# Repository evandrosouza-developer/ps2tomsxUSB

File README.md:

# STM32: PS/2 to MSX Keyboard Converter

# Introduction

First of all, to people who use or had used MSX, welcome, bem-vindos, welkom, bienvenidos, добро пожаловать, 환영하다 and ようこそ, to visit my repository.

Instead of an application to this old japanese home computer standards is not so widely useful in nowadays, I made this to learn STM32 hardware and software technics, and I'd like it to be useful and let us back in time and make our MSX computer jewlers work with joyful to our pleasure.

The MSX Keyboard enviroment components (PS/2 to MSX Keyboard Converter, MSX Keyboard subsystem Emulator and the modifyed TIO - A simple terminal) are fully functional and debugged and here I used a lot of concepts that, IMHO could be used as idea sources to your applications.  

# Lets do it!

This interface has the function of connect a PS/2 keyboard (or a USB one in compatibility mode) as source to TTL zero (low state) active matrix based computers, like MSX and ZX-Spectrum as destination. It is meant to connect a keyboard, which only provides a PS/2 connector, to a MSX (or any one that have a up to 15 active columns and reads zeroes througth 8 bits - up to 15 x 8 matrix) computer.  

The differencial of this design is to allow user to customize and do a hot update of the database layout of this PS/2 Keyboard, as like as the MSX one, through an USB (or async serial) interface and a tty terminal on host side.  

The default database mappings for the keyboard layouts are:

- Source (PS/2 keyboard): 275 (ABNT2 layout - Brazilian Technical Norms Association);

- Target: Brazilian Sharp/Epcom Hotbit HB8000 MSX.  

This firmware was made to support both Blue Pill and Black Pill and it is part of the PS/2 to MSX Converter Enviroment, all of them in my github page, that consists:
```
1)The PS/2 to MSX Keyboard Converter itself, which contains:
1.1) The firmware with source files;
1.2) Doxygen full firmware documentation;
1.3) Schematics and PCB design:
1.3.1) Electronics part Schematics with Kicad files;
1.3.2) Single sided PCB layout with Kicad files and complete set of Gerber files;
1.4) The performance tests of this one are inside the PS/2 to MSX Converter Tester folder.

2)The PS/2 to MSX Converter Tester, which contains:
2.1) The firmware with source files;
2.2) Doxygen full firmware documentation;
2.3) Schematics design with Kicad files;
2.4) The performance tests of the PS/2 to MSX Keyboard Converter are located here.

3) Open tool to create/modify the Database (Translation tables to map from PS/2 Scan Codes to MSX Matrix Codes)
in excel, but it has compatible macros to be executed by Libre Office, Open Office and so on.

4) Tini TTY I/O - `tio` (Linux app with source files) to communicate with console and easily allowing the
user to use it with different keyboard layouts and languages.
```
In case of STM32F103C8T6 (Flash 64K RAM 20K) Blue Pill, you have to aplly STM32F103C6T6 (Flash 32K RAM 10K) without change anything else.

In case of Black Pill, the base system is STM32F401CCU6 so, to use a more memory one, just follow the same instructions here.

This firmware powers and has been tested on the following Windows PS/2 keyboards, with brazilian 275 layout:  
- Compaq RT235BTWBR;  
- Clone KE11090749;  
- Clone #09100.  
  
The inspiring code for the PS/2 module, a PS/2 to USB keyboard adapter, was originally developed based on Cherry G80-3000LSMDE.  

# Why not STM32F103C8T6 Blue Pill?

Because Blue Pill has no 5V tolerant pins available to connect PS/2 + MSX + Serial + USB, unlike Black Pill. Even serial (UART) was feasibled using a 3.3V only port.  
Although, this limitation came with a bonus: The need of a cheaper and greater availability 32KB flash MCU: STM32F103C6T6  

# Dependencies

- `libopencm3`
- `arm-none-eabi-gcc`
- `arm-none-eabi-binutils`

If you plan to debug:
- `arm-none-eabi-gdb`
- `stlink + openocd`

Obs.: If you plan to keep only one copy of LibopenCM3 in your computer, I strongly suggest you to setup the variable OPENCM3_DIR in our system enviroment.

# Preparations

After cloning the repository you need to make the following procedure:

Go to libopencm3 you cloned (eg: cd libopencm3) and make it to be useful by typing:

```
cd libopencm3
make TARGETS='stm32/f1 stm32/f4'
```

Go to this ps2-msx-kb-conv (PS/2 to MSX Converter) project folder and assure that you choose the right target MCU in the system.h file line 69, and make, as follows:

With a plain text editor:
```
#define MCU                       STM32F401
or
#define MCU                       STM32F103
```

Save the file, and,  
Create the image file to be sent to the MCU (Micro Controller Unit):

```
make
```
The created image, compiled with the Arm GNU Toolchain 14.2.Rel1 Released: December 10, 2024, on an aarch64 debian bullseye linux computer is created with the following characteristics, according to the choosen MCU:
```
arm-none-eabi-size ps2-msx-kb-convF4.elf
   text	   data	    bss	    dec	    hex	filename
35796	    384	   8436	  44616	   ae48	ps2-msx-kb-convF4.elf

arm-none-eabi-size ps2-msx-kb-convF1.elf
   text	   data	    bss	    dec	    hex	filename
  27152	    352	   2492	  29996	   752c	ps2-msx-kb-convF1.elf

```

# Hardware and Setup

## Hardware and Setup for Blue Pill:

You will obviously need a STM32F103C6T6 or a STM32F103C8T6 (F1 chip). I have used chinese blue pills. The software was made aiming in use of compatible processors, like GD32 for example. 
  
The software was made considering 8.000Mhz oscillator crystal, to clock the STM32 microcontroller chip at 72MHz. I tested with both STM32F103C6T6 and STM32F103C8T6.

The connections are:

1) PS/2 Keyboard:

- Clock Pin PA12 - Connect to PS/2 mini-din 45322 pin 5 throught R16;  
- Data Pin PA9 - Connect to PS/2 mini-din pin 1 throught R18;    
- +5V PS/2 power - Connect collector of Q2 to mini-din pin 4;  
- GND - Connect GNDD (Digital Ground) to mini-din pin 3.

2) MSX computer:

Obs.: You have to access PPI Ports B0 to B7 (Lines X0 to X7), Port C0 to C3 (Y0 to Y3), Port C6 (Caps Lock, pin 11 of DIP package), and for Russian, Arabic, Korean and Japanese Computers (Cyrillic and Kana alphabets), you have to get access to YM2149/AY3-8910 IOB7, pin 6 of DIP package, or, if your MSX is equipped with S1985(MSX-SYSTEM II), you have to have granted access to pins 71 and 72.  
- Y3 - Connect to MSX PPI 8255 Signal PC3 (HB-8000 CI-15 Pin 17 / XP-800 CI-4 Pin 17);  
- Y2 - Connect to MSX PPI 8255 Signal PC2 (HB-8000 CI-15 Pin 16 / XP-800 CI-4 Pin 16);  
- Y1 - Connect to MSX PPI 8255 Signal PC1 (HB-8000 CI-15 Pin 15 / XP-800 CI-4 Pin 15);  
- Y0 - Connect to MSX PPI 8255 Signal PC0 (HB-8000 CI-15 Pin 14 / XP-800 CI-4 Pin 14);  
- X7 - Connect to MSX PPI 8255 Signal PB7 (HB-8000 CI-15 Pin 25 / XP-800 CI-4 Pin 25);  
- X6 - Connect to MSX PPI 8255 Signal PB6 (HB-8000 CI-15 Pin 24 / XP-800 CI-4 Pin 24);  
- X5 - Connect to MSX PPI 8255 Signal PB5 (HB-8000 CI-15 Pin 23 / XP-800 CI-4 Pin 23);  
- X4 - Connect to MSX PPI 8255 Signal PB4 (HB-8000 CI-15 Pin 22 / XP-800 CI-4 Pin 22);  
- X3 - Connect to MSX PPI 8255 Signal PB3 (HB-8000 CI-15 Pin 21 / XP-800 CI-4 Pin 21);  
- X2 - Connect to MSX PPI 8255 Signal PB2 (HB-8000 CI-15 Pin 20 / XP-800 CI-4 Pin 20);  
- X1 - Connect to MSX PPI 8255 Signal PB1 (HB-8000 CI-15 Pin 19 / XP-800 CI-4 Pin 19);  
- X0 - Connect to MSX PPI 8255 Signal PB0 (HB-8000 CI-15 Pin 18 / XP-800 CI-4 Pin 18);  
- Caps LED - Connect to MSX PPI 8255 Signal PC6 (HB-8000 CI-15 Pin 11 / XP-800 CI-4 Pin 11) or S1985 Pin 71;  
- Kana LED - Connect to MSX YM2149 or AY3-8910 IOB7, pin 6 of DIP package or S1985 Pin 72. If the MSX doesn't have this indicator LED, you can leave it open, as it already has an internal pull-up connection. In brazilian, argentinian and most european MSX, for example, this is a non-connect pin.   

3) Serial console:
 It is the only option for console available if you are using Blue Pill. See "Why not STM32F103C8T6 Blue Pill?".

  The connection is needed only to update internal PS/2 to MSX key mapping Database.  
  Config: 115200, 8, n, 1 (115200 bps, 8 bits, no parity, 1 stop bit);  
  Tx: A2  
  Rx: A3  

  *******************************************************************************************************

  Obs.: It is a only 3.3V port, compatible to TTL levels, so do NOT use it with "1" level higher than 3.3V!!

  *******************************************************************************************************

 About physical connection: The connection has to be done with TX of your host system connected with RX of the PS/2 to MSX Keyboard Converter (device), and the device's TX has to be connected to host's RX.

## Hardware and Setup for Black Pill:

You will obviously need a a F4 chip (STM32F401CCU6 or up, if using WeAct Mini F4 compatible black pill).

The software was made considering 25.000Mhz oscillator crystal, to clock the STM32 microcontroller chip at 84MHz. I tested with both STM32F401CCU6 and STM32F401CDU6.

The connections are:

1) PS/2 Keyboard (J3- PS/2 Port) :

- PS/2 power - Pin 1 - Connect to PS/2 mini-din 45322 pin 4;  
- Clock      - Pin 2 - Connect to PS/2 mini-din 45322 pin 5;  
- Data       - Pin 3 - Connect to PS/2 mini-din 45322 pin 1;  
- GNDD       - Pin 4 - Connect to PS/2 mini-din 45322 pin 3.  

2) MSX computer:

Obs.: You have to access PPI Ports B0 to B7 (Lines X0 to X7), Port C0 to C3 (Y0 to Y3), Port C6 (Caps Lock, pin 11 of DIP package), and for Russian and Japanese Computers (Cyrillic and Kana alphabets), you have to get access to YM2149/AY3-8910 IOB7, pin 6 of DIP package, or, if your MSX is equipped with S1985(MSX-SYSTEM II), you have to have granted access to pins 71 and 72.  

- Y3 - Connect to MSX PPI 8255 Signal PC3 (HB-8000 CI-15 Pin 17 / XP-800 CI-4 Pin 17);  
- Y2 - Connect to MSX PPI 8255 Signal PC2 (HB-8000 CI-15 Pin 16 / XP-800 CI-4 Pin 16);  
- Y1 - Connect to MSX PPI 8255 Signal PC1 (HB-8000 CI-15 Pin 15 / XP-800 CI-4 Pin 15);  
- Y0 - Connect to MSX PPI 8255 Signal PC0 (HB-8000 CI-15 Pin 14 / XP-800 CI-4 Pin 14);  
- X7 - Connect to MSX PPI 8255 Signal PB7 (HB-8000 CI-15 Pin 25 / XP-800 CI-4 Pin 25);  
- X6 - Connect to MSX PPI 8255 Signal PB6 (HB-8000 CI-15 Pin 24 / XP-800 CI-4 Pin 24);  
- X5 - Connect to MSX PPI 8255 Signal PB5 (HB-8000 CI-15 Pin 23 / XP-800 CI-4 Pin 23);  
- X4 - Connect to MSX PPI 8255 Signal PB4 (HB-8000 CI-15 Pin 22 / XP-800 CI-4 Pin 22);  
- X3 - Connect to MSX PPI 8255 Signal PB3 (HB-8000 CI-15 Pin 21 / XP-800 CI-4 Pin 21);  
- X2 - Connect to MSX PPI 8255 Signal PB2 (HB-8000 CI-15 Pin 20 / XP-800 CI-4 Pin 20);  
- X1 - Connect to MSX PPI 8255 Signal PB1 (HB-8000 CI-15 Pin 19 / XP-800 CI-4 Pin 19);  
- X0 - Connect to MSX PPI 8255 Signal PB0 (HB-8000 CI-15 Pin 18 / XP-800 CI-4 Pin 18);  
- Caps LED - Connect to MSX PPI 8255 Signal PC6 (HB-8000 CI-15 Pin 11 / XP-800 CI-4 Pin 11) or S1985 Pin 71;  
- Kana LED - Connect to MSX YM2149 or AY3-8910 IOB7, pin 6 of DIP package or S1985 Pin 72. If the MSX doesn't have this indicator LED, you can leave it open, as it already has an internal pull-up connection. In brazilian, argentinian and most european MSX, for example, this is a non-connect pin.   
  
3) USB Type C: Needed only to update internal PS/2 to MSX key mapping Database. To create this Intel Hex file, better to use the Macro based Excel file, so you have to trust and enable macro excecution in excel app. The USB cable is the same as you use with yor mobile phone (USB Type-A Male x USB Type C Male).  
  
4) Serial console: Same observations of USB are applicable here, with exception of the cable itself. Here the connection has to be done with TX of your host system connected with RX of the PS/2 to MSX Keyboard Converter (device), and the device's TX has to be connected to host's RX.  
   Config: 115200, 8, n, 1 (115200 bps, 8 bits, no parity, 1 stop bit);  
   Tx: A9  
   Rx: A10  

  *******************************************************************************************************

  Obs.: It uses a 5V tolerant port, which is compatible to TTL levels, so do NOT use it with "1" level higher than 5V!!

  *******************************************************************************************************  

# The Database structure: Keyboard from/to mapping

This design was developed to connect, as default, an ABNT-2 brazilian PC keyboard to the brazilian MSX Sharp/Epcom HB-8000, but it is very easy to apply a hot change of its mapping:

- You have to compile and upload this new database to the Converter. This task is easily managed with the help of a Database compiler: The macro enabled excel file named `PS2toMSX_Database_Compiler.xlsm`.

To edit and compile the Database file, both source and target keyboard layouts, I prepaired a dedicated "key assembler in excel", so I can boldly recommend you to use the excel file `PS2toMSX_Database_Compiler.xlsm` available at github page.  
The Database Compiler file has 3 sheets: One for HB-8000, the second as XP-800 and the third one as an International MSX. Unfortunately, the last one was not tested. Just fillin the table, click on the keyboard image of upper left of the current sheet and wait for VBA has been concluded.  
The Database Compiler excel file exports the IHD.hex file (Intel Hex Database) to be hot applyed to PS/2 to MSX Keyboard Converter's Console, when this one boots up with no PS/2 Keyboard pluged in. Just follow console instructions. You may use `tio` as a terminal linux app to upload it.  
 
*******************************************************************  
<div align= "center"><strong>IMPORTANT</strong>  </div> 
<div align="left">If you are using Blackpill board and are uploading Database through USB, please do a FULL DISCONNECT (ALL lines INCUDING POWER) from MSX,  to avoid short circuit through power supply lines!  

I strongly suggest that the Black Pill board be pulled out from PS/2 to MSX Keyboard Converter board, as the power is going to be supplyed from USB and the heavy task to reconnect all will be saved, if you decided not to use the connector on the J1, which would simplify and make the task much safer.

*******************************************************************  

## Technical details about the Database structure

	There are 320 lines, so this structure is capable of manage up to 159 PS/2 keys, each key with make and break codes.

	The first and last lines are reserved for control (Database version, Database unavailable: seek next, double consistensy check, among others);
	
	On the first line there are information related to this Database version:
	- Bytes 0, 1 and 2: Database version ("0x01", "0x00", "0xFF")
	- Byte 3: Mapped function. Description:  
	  |  (bits 7-6): Reserved - keep it at high state;  
	  |  (bit 5): default value of enable_xon_xoff (true to enable it);  
	  |  (bit 4): default value of ps2numlockstate at power up (true to enable it);  
	  |  (bits 3-0): y_dummy (non valid colunm) - default value is 15 (0b1111);  
	- Bytes 4-7: Reserved - Keep it as 0xFFFFFFFF;
        When this copy of the Database is let unavailable, the first line becomes ("0x00", "0x00", "0x00", "0x00", "0x01", "0x02", 
	"0x04", "0x08"), meaning to seek the next one.

	On the line 319 (the last one) there are information related to this Database integrity:  
	- Bytes 0-5: Reserved - Keep each byte as 0xFF;  
	- Byte 6: CheckSum (Integrity);  
	- Byte 7: bcc (a vertical parity used for integrity);  

	Line 1 starts the raw of the Database:  
  
	The three first columns of each line are the mapped PS/2 scan codes;  
  
	The 4th column is The Control Byte, detailed bellow:   
	CONTROL BYTE:  
	- High nibble is Reserved;  
	- (bit 3) Combined Shift;  
	- (bit 2) Reserved-Not used;  
	- (bits 1-0) Modifyer Type:  
	  |		0 - Default mapping  
	  |		1 - NumLock Status+Shift changes  
	  |		2 - PS/2 Shift  
	  |		3 - Reserved-Not used  

	This table has 3 modifyers: Up two MSX keys are considered to each mapping behavior modifying:
	- 5th and 6th columns have the mapping 0 - "Default mapping";  
	- 7th and 8th columns share mappings:  1 and 2:  
	  |                                    1 - "NumLock Status+Shift changes";  
	  |                                    2 - "PS/2 Shift", where I need to release the sinalized Shift in PS/2 to the MSX and put the code key, and so, release them, reapplying the Shift key, deppending on the initial state;  

	Each column has a MSX encoded key, with the following structure:
	- (bits 7-4) MSX Y PPI 8255 PC3-0 is sent to a BCD decoder with OC outputs, for example:  
	  |	In the case of Hotbit HB8000, the keyboard scan is done as a 9 columns scan, CI-16 7445N 08 to 00;  
	  |	If equals to value stored at bits 3-0 of byte 3 of the Database file, there is no MSX key mapped.  
	- (bit 3) => 0: keypress / 1: key release;             
	- (bits 2-0) MSX X, ie, which bit of the PPI 8255 PB7-0 will carry information of bit 3 (keypress/key release).  

# Download your code to hardware

Use a ST-Link v2 Programmer (or similar), Black Magic Probe or another Serial Wire supported tool to flash the program using `make flash` onto the STM32.

If you choose a Black Pill, even you don't have plans to develop, you earn a bonus: you will not have the need of a dedicated programmer like ST-Link, J-link or Black Magic Probe to download your code, as STM32F4x1 MiniF4 already comes with DFU (Device Firmware Upgrade) available in the system ROM to do so through USB. So, on linux, just follow these steps:

1) Unplug the MSX connection or take off the Black Pill from the PS/2 to MSX Converter Main Board;  
2) Install dfu-util. This example is for Debian derivated Linux (Debian, Ubuntu, Mint, etc):
`sudo apt install dfu-util`  
3) Make sure the chip is at least 25°C (you may let it working for a while and help with the heat of your finger), because it uses internal oscillator to clock USB, factory trimmed to 25°C;  
4) Plug the USB cable to your computer and the STM32F4 board while holding both NRST and BOOT0;  
5) Then release BOOT0 AFTER 0.5 second you released NRST;  
6) Now you can see a new USB device in your linux enviroment, through `lsusb` command: 0483:df11. Run the command to flash the code itself:
`dfu-util -d 0483:df11 -a 0 -s 0x08000000 -D ps2-msx-kb-convF4.bin`  
7) Unplug the USB cable, undo the step 1 and power on the device to run the code.  
  
On windows you can download STM32CubeProg on ST site, replacing step 2. You have to adjust step 6 to this tool. Please follow ST instructions.

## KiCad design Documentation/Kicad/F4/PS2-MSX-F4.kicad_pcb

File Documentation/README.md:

# STM32: PS/2 to MSX Keyboard Converter

# Introduction

First of all, to people who used MSX, welcome, bem-vindos, welkom, bienvenidos, добро пожаловать, 환영하다 and ようこそ, to visit my repository.

Instead of an application to this old japanese home computer standards is not so widely useful in nowadays, I made this to learn STM32 hardware and software technics, and I'd like it to be useful and let us back in time and make our MSX computer jewlers work with joyful to our pleasure.

The MSX Keyboard enviroment components (PS/2 to MSX Keyboard Converter, MSX Keyboard subsystem Emilator and the modifyed TIO - A simple terminal) are fully functional and debugged and here I used a lot of concepts that, IMHO could be used as idea sources to your applications.

# Lets do it!

This interface has the function of connect a PS/2 keyboard (or a USB one in compatibility mode) as source to zero active matrix based computers, like MSX and ZX-Spectrum as destination. It is meant to connect a keyboard, which only provides a PS/2 connector, to a MSX (or any one that have a up to 15 active columns and reads zeroes througth 8 bits - up to 15 x 8 matrix) computer.

The differencial of this design is to allow user to customize and update the database layout of this PS/2 Keyboard, as like as the MSX one, through an USB (or async serial) interface and a tty terminal on host side.

To edit the Database file, both source and target keyboard layouts, I prepaired a dedicated "key assembler in excel", so I can boldly recommend you to use the excel file `PS2toMSX_Database_Compiler.xlsm` available at github page.

The default database mappings for the keyboard layouts are:

- Source (PS/2 keyboard): 275 (ABNT2 layout - Brazilian Technical Norms Association);

- Target: Brazilian Sharp/Epcom Hotbit HB8000 MSX.

This firmware was made to support both Blue Pill and Black Pill and it is part of the PS/2 to MSX Converter Enviroment, all of them in my github page, that consists:
```
1)The PS/2 to MSX Keyboard Converter itself, which contains:
1.1) The firmware with source files;
1.2) Schematics and PCB design:
1.2.1) Electronics part Schematics with Kicad files;
1.2.2) Single sided PCB layout with Kicad files and complete set of Gerber files;

2)The PS/2 to MSX Converter Tester, which contains:
2.1) The firmware with source files;
2.2) Schematics design with Kicad files;

3) Tool to create/modify the Database (Translation tables to map from PS/2 Scan Codes to MSX Matrix Codes) in excel, but it has compatible macros to be executed by Libre Office, Open Office, Star Office and so on.

4) Tini TTY I/O - tio (Linux app with source files) to communicate with console and easily allowing the user to use it with different keyboard layouts and languages.
```
In case of STM32F103C8T6 (Flash 64K RAM 20K) Blue Pill, you have to aplly STM32F103C6T6 (Flash 32K RAM 10K) without change anything else.

In case of Black Pill, the base system is STM32F401CCU6 so, to use a more memory one, just follow the same instructions here.

This firmware powers and has been tested on the following Windows keyboards, with brazilian 275 layout:

- Compaq RT235BTWBR;

- Clone KE11090749;

- Clone #09100.

The original code was originally developed based on:

- Cherry G80-3000LSMDE.

## Why not STM32F103C8T6 Blue Pill?

Because Blue Pill has no 5V tolerant pins available to connect PS/2 + MSX + Serial + USB, unlike Black Pill. Even serial (UART) was feasibled using a 3.3V only port.

Although, this limitation came with a bonus: The need of a cheaper and greater avaiability 32KB flash MCU: STM32F103C6T6

# Dependencies

- `arm-none-eabi-gcc`
- `arm-none-eabi-gdb`
- `arm-none-eabi-binutils`
- `stlink + openocd (if you want to debug)`
- `libopenmcm3`

Obs.: If you plan to keep only one copy of LibopenCM3 in your computer, I really suggest you to create the variable OPENCM3_DIR in our system enviroment.

# Preparations

After cloning the repository you need to make the following preparations:

Go to libopencm3 you cloned (eg: cd libopencm3) and make it to be useful by typing:

```
cd libopencm3
make TARGETS='stm32/f1 stm32/f4'
```

Go to your PS/2 to MSX Converter Tester project folder and assure that you choose the right target MCU in the system.h file line 69, and make, as follows:

With a text editor:
```
#define MCU                       STM32F401
or
#define MCU                       STM32F103
```

Save the file, and,

Create the image file to be sent to the MCU (Micro Controller Unit):

```
make
```
The created image compiled with an Arm GNU Toolchain 12.2.MPACBTI-Bet1 (Build arm-12-mpacbti.16)) 12.2.0 version on an aarch64 debian bullseye linux computer is created with the following characteristics, according to the choosen MCU:
```
arm-none-eabi-size ps2-msx-kb-convF4.elf
   text	   data	    bss	    dec	    hex	filename
  35604      60    8120   43784    ab08 ps2-msx-kb-convF4.elf

arm-none-eabi-size ps2-msx-kb-convF1.elf
   text	   data	    bss	    dec	    hex	filename
  26956      24    2176   29156    71e4 ps2-msx-kb-convF1.elf

```

# Hardware and Setup

## Hardware and Setup for Blue Pill:

You will obviously need a STM32F103C6T6 or a STM32F103C8T6 (F1 chip). I have used chinese blue pills. The software was made aiming in use of compatible processors, like GD32 for example. 
  
The software was made considering 8.000Mhz oscillator crystal, to clock the STM32 microcontroller chip at 72MHz. I tested with both STM32F103C6T6 and STM32F103C8T6.

The connections are:

1) PS/2 Keyboard:

- Clock Pin PA12 - Connect to PS/2 mini-din 45322 pin 5 throught R16;

- Data Pin PA9 - Connect to PS/2 mini-din pin 1 throught R18;

- +5V PS/2 power - Connect collector of Q2 to mini-din pin 4;

- GND - Connect GNDD (Digital Ground) to mini-din pin 3.

2) MSX computer:

Obs.: You have to access PPI Ports B0 to B7 (Lines X0 to X7), Port C0 to C3 (Y0 to Y3), Port C6 (Caps Lock, pin 11 of DIP package), and for Russian and Japanese Computers (Cyrillic and Kana alphabets), you have to get access to YM2149 IOB7, pin 6 of DIP package.

- Y3 - Connect to MSX PPI 8255 Signal PC3;

- Y2 - Connect to MSX PPI 8255 Signal PC2;

- Y1 - Connect to MSX PPI 8255 Signal PC1;

- Y0 - Connect to MSX PPI 8255 Signal PC0;

- X7 - Connect to MSX PPI 8255 Signal PB7 (Hotbit HB-8000 CI-15 Pin 25);

- X6 - Connect to MSX PPI 8255 Signal PB6 (Hotbit HB-8000 CI-15 Pin 24);

- X5 - Connect to MSX PPI 8255 Signal PB5 (Hotbit HB-8000 CI-15 Pin 23);

- X4 - Connect to MSX PPI 8255 Signal PB4 (Hotbit HB-8000 CI-15 Pin 22);

- X3 - Connect to MSX PPI 8255 Signal PB3 (Hotbit HB-8000 CI-15 Pin 21);

- X2 - Connect to MSX PPI 8255 Signal PB2 (Hotbit HB-8000 CI-15 Pin 20);

- X1 - Connect to MSX PPI 8255 Signal PB1 (Hotbit HB-8000 CI-15 Pin 19);

- X0 - Connect to MSX PPI 8255 Signal PB0 (Hotbit HB-8000 CI-15 Pin 18);

- Caps LED - Connect to MSX PPI 8255 Signal PC6 (Hotbit HB-8000 CI-15 Pin 11 / Expert XP-800 CI-4);

- Kana LED - Connect to MSX YM2149 IOB7, pin 6 of DIP package. If the MSX doesn't have this, you can leave it open, as it already has an internal pull-up connection.

3) Serial console:
 It is the only option for console available if you are using Blue Pill. Vide ## Why not STM32F103C8T6 Blue Pill?

 The connection is needed only to update internal PS/2 to MSX key mapping Database. To create this Intel Hex file, better to use the Macro based Excel file, so you have to trust and enable macro excecution in excel app. 

  Config: 115200, 8, n, 1 (115200 bps, 8 bits, no parity, 1 stop bit);

  Tx: A2

  Rx: A3

  *******************************************************************************************************

  Obs.: It is a only 3.3V port, compatible to TTL levels. Do not use it with "1" level higher than 3.3V!!

  *******************************************************************************************************

 About physical connection: The connection has to be done with TX of your host system connected with RX of the PS/2 to MSX Keyboard Converter (device), and the device's TX has to be connected to host's RX.

## Hardware and Setup for Black Pill:

You will obviously need a a F4 chip (STM32F401CCU6 or up, if using WeAct Mini F4 compatible black pill).

The software was made considering 25.000Mhz oscillator crystal, to clock the STM32 microcontroller chip at 84MHz. I tested with both STM32F401CCU6 and STM32F401CDU6.

The connections are:

2) PS/2 Keyboard (J3- PS/2 Port) :

- PS/2 power - Pin 1 - Connect to PS/2 mini-din 45322 pin 4;

- Clock      - Pin 2 - Connect to PS/2 mini-din 45322 pin 5;

- Data       - Pin 3 - Connect to PS/2 mini-din 45322 pin 1;

- GNDD       - Pin 4 - Connect to PS/2 mini-din 45322 pin 3.

3) MSX computer:

Obs.: You have to access PPI Ports B0 to B7 (Lines X0 to X7), Port C0 to C3 (Y0 to Y3), Port C6 (Caps Lock, pin 11 of DIP package), and for Russian and Japanese Computers (Cyrillic and Kana alphabets), you have to get access to YM2149 IOB7, pin 6 of DIP package.

- Y3 - Connect to MSX PPI 8255 Signal PC3 (HB-8000 CI-15 Pin 17 / XP-800 CI-4 Pin 17);

- Y2 - Connect to MSX PPI 8255 Signal PC2 (HB-8000 CI-15 Pin 16 / XP-800 CI-4 Pin 16);

- Y1 - Connect to MSX PPI 8255 Signal PC1 (HB-8000 CI-15 Pin 15 / XP-800 CI-4 Pin 15);

- Y0 - Connect to MSX PPI 8255 Signal PC0 (HB-8000 CI-15 Pin 14 / XP-800 CI-4 Pin 14);

- X7 - Connect to MSX PPI 8255 Signal PB7 (HB-8000 CI-15 Pin 25 / XP-800 CI-4 Pin 25);

- X6 - Connect to MSX PPI 8255 Signal PB6 (HB-8000 CI-15 Pin 24 / XP-800 CI-4 Pin 24);

- X5 - Connect to MSX PPI 8255 Signal PB5 (HB-8000 CI-15 Pin 23 / XP-800 CI-4 Pin 23);

- X4 - Connect to MSX PPI 8255 Signal PB4 (HB-8000 CI-15 Pin 22 / XP-800 CI-4 Pin 22);

- X3 - Connect to MSX PPI 8255 Signal PB3 (HB-8000 CI-15 Pin 21 / XP-800 CI-4 Pin 21);

- X2 - Connect to MSX PPI 8255 Signal PB2 (HB-8000 CI-15 Pin 20 / XP-800 CI-4 Pin 20);

- X1 - Connect to MSX PPI 8255 Signal PB1 (HB-8000 CI-15 Pin 19 / XP-800 CI-4 Pin 19);

- X0 - Connect to MSX PPI 8255 Signal PB0 (HB-8000 CI-15 Pin 18 / XP-800 CI-4 Pin 18);

- Caps LED - Connect to MSX PPI 8255 Signal PC6 (HB-8000 CI-15 Pin 11 / XP-800 CI-4 Pin 11);

- Kana LED - Connect to MSX YM2149 IOB7, pin 6 of DIP package. If the MSX doesn't have this, you can leave it open, as it already has an internal pull-up connection.

3) USB Type C: Needed only to update internal PS/2 to MSX key mapping Database. To create this Intel Hex file, better to use the Macro based Excel file, so you have to trust and enable macro excecution in excel app. The USB cable is the same as you use with yor mobile phone (USB Type-A Male x USB Type C Male).

4) Serial console: Same observations of USB are applicable here, with exception of the cable itself. Here the connection has to be done with TX of your host system connected with RX of the PS/2 to MSX Keyboard Converter (device), and the device's TX has to be connected to host's RX.

  Config: 115200, 8, n, 1 (115200 bps, 8 bits, no parity, 1 stop bit);

  Tx: A9

  Rx: A10

  *******************************************************************************************************

  Obs.: It uses a 5V tolerant port, which is compatible to TTL levels. Do not use it with "1" level higher than 5V!!

  *******************************************************************************************************

# Technical details about the Database structure

The structure of the Database is:

	There are 320 lines, so this structure is capable of manage up to 159 PS/2 keys with their respective make and break codes.

	The first and last lines are reserved for control (Database version, Database unavailable: seek next, double consistensy
	check, among others);
	
	On the first line there are information related to this Database version:
	- Bytes 0, 1 and 2: Database version ("0x01", "0x00", "0xFF")
	- Byte 3: Mapped function. Description:
	    (bit 7-6): Reserved - keep it at high state;
	    (bit 5): default value of enable_xon_xoff;
	    (bit 4): default value of ps2numlockstate at power up;
	    (bits 3-0): y_dummy (non valid colunm);
	- Bytes 4-7: Reeserved - Keep it as 0xFFFFFFFF;

	On the line 319 (the last one) there are information related to this Database integrity:
	- Bytes 0-5: Reeserved - Keep each byte as 0xFF;
	- Byte 6: CheckSum (Integrity);
	- Byte 7: bcc (a type of vertical parity used for integrity);

	Starting on line 1, the raw of the Database:
  
	The three first columns of each line are the mapped scan codes;
	The 4th column is The Control Byte, detailed bellow:
	CONTROL BYTE:
		High nibble is Reserved;
		(bit 3) Combined Shift;
		(bit 2) Reserved-Not used;
		(bits 1-0) Modifyer Type:
		.0 - Default mapping
		.1 - NumLock Status+Shift changes
		.2 - PS/2 Shift
		.3 - Reserved-Not used

	This table has 3 modifyers: Up two MSX keys are considered to each mapping behavior modifying:
	5th and 6th columns have the mapping ".0 - Default mapping";
	7th and 8th columns share mappings   ".1" and ".2":
	                                     ".1 - NumLock Status+Shift changes";
	                                     ".2 - PS/2 Shift", where I need to release the sinalized Shift in PS/2 to the MSX and put the
					           coded key, and so, release them, reapplying the Shift key, deppending on the initial state;

	Each column has a MSX coded key, with the follwing structure:
	(Bit 7:4) MSX Y PPI 8255 PC3:0 is send to an OC outputs BCD decoder, for example:
					     In the case of Hotbit HB8000, the keyboard scan is done as a 9 columns scan, CI-16 7445N 08 to 00;
					     If equals to 1111 (Y=15), there is no MSX key mapped.
					     (Bit 3)	 0: keypress
 							 1: key release;
           
	(Bit 2:0) MSX X, ie, which bit will carry the key, to be read by PPI 8255 PB7:0.

# Download your code to hardware

Use a ST-Link v2 Programmer (or similar), Black Magic Probe or another Serial Wire supported tool to flash the program using `make flash` onto the STM32.

If you choose a Black Pill, even you don't have plans to develop, you earn a bonus: you will not have the need of a dedicated programmer like ST-Link, J-link or Black Magic Probe to download your code, as STM32F4x1 MiniF4 already comes with DFU (Device Firmware Upgrade) available in the system ROM to do so through USB. So, on linux, just follow these steps:

1) Install dfu-util. This example is for Debian derivated Linux (Debian, Ubuntu, Mint, etc):
`sudo apt install dfu-util`

2) Make sure the chip is at least 25°C (you may let it working for a while and help with the heat of your finger), because it uses internal oscillator to clock USB, factory trimmed to 25°C;

3) Plug the USB cable to your computer and the STM32F4 board while holding both NRST and BOOT0;

4) Then release BOOT0 AFTER 0.5 second you released NRST;

5) Now you can see a new USB device in your linux enviroment: 0483:df11. Run the command to flash the code itself:
`dfu-util -d 0483:df11 -a 0 -s 0x08000000 -D ps2-msx-kb-convF4.bin`

6) Unplug the USB cable and power on the device to run the code.

On windows you can download STM32CubeProg on ST site, replacing step 1. You have to adjust step 6 to this tool. Please follow ST instructions.

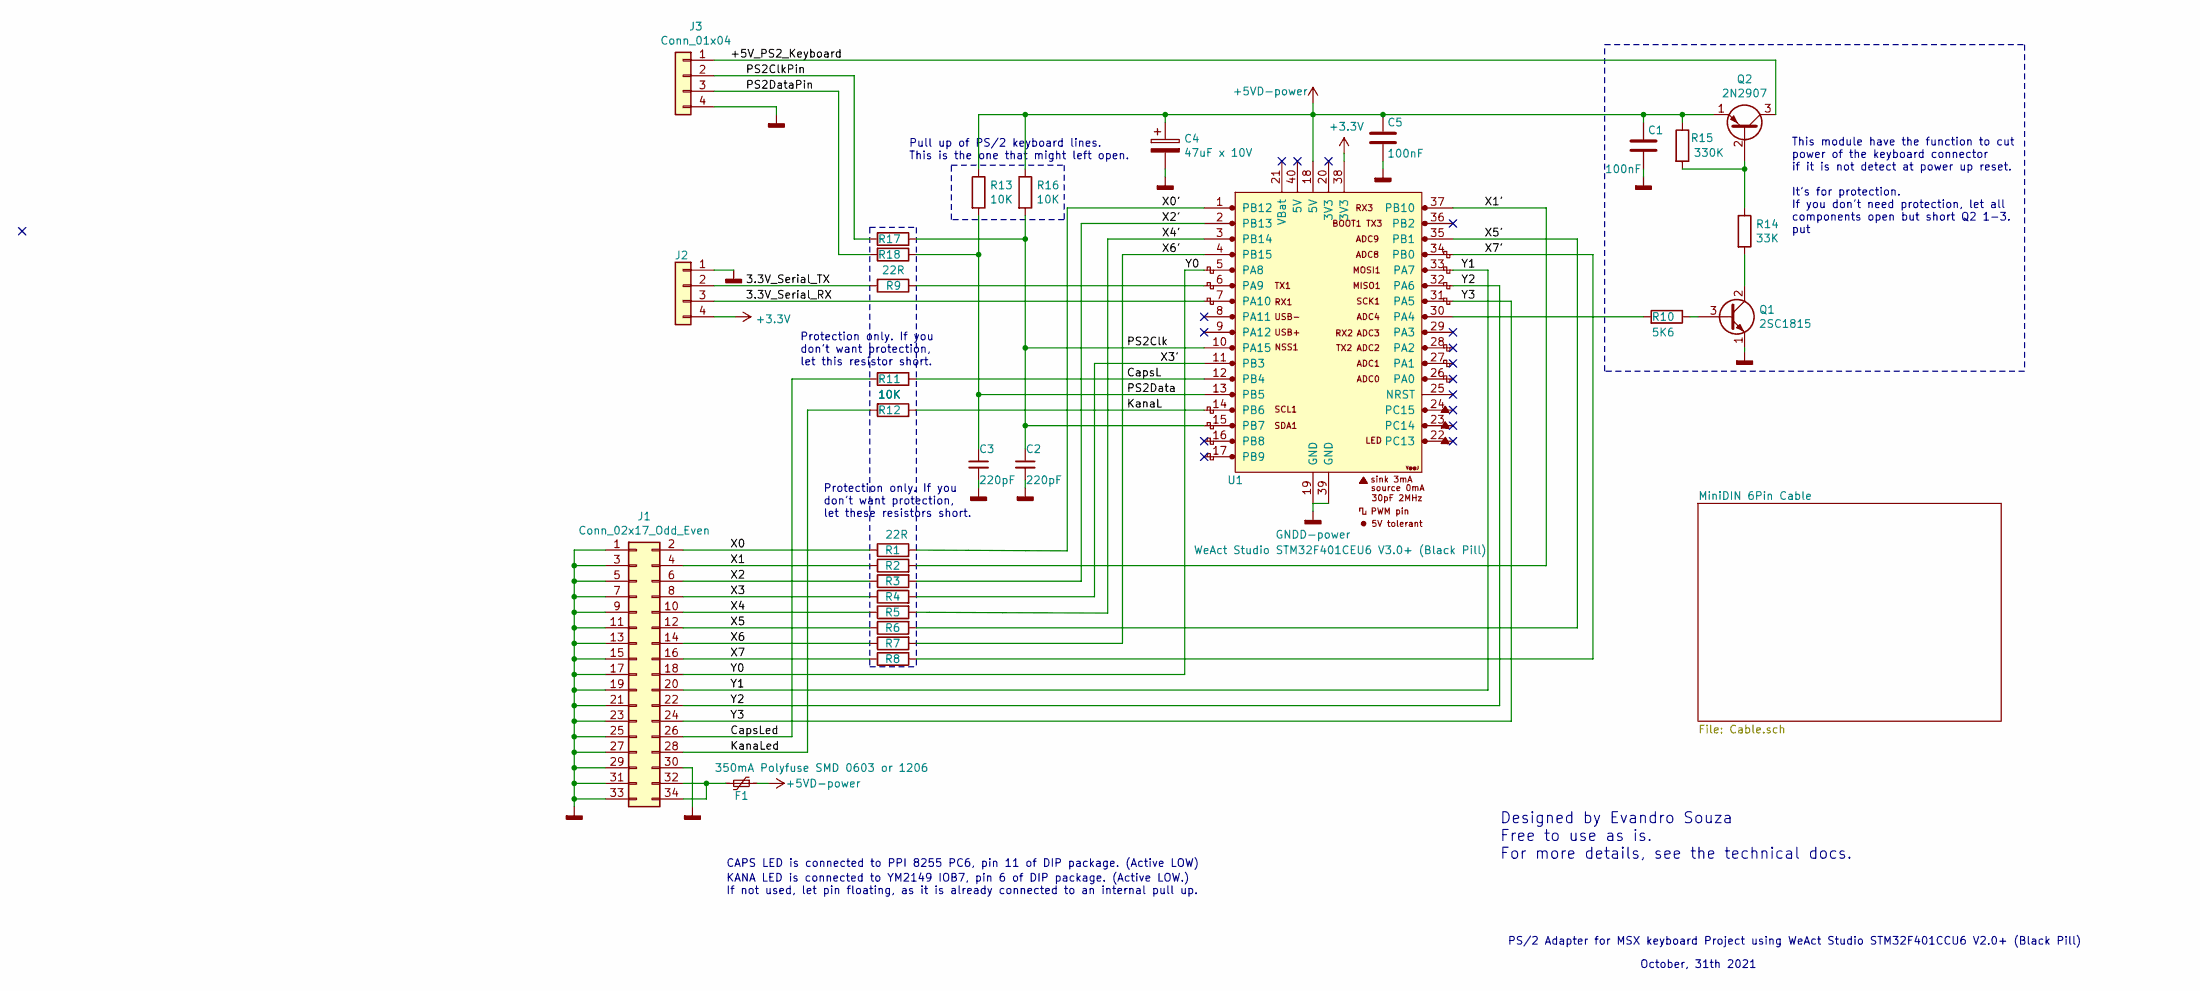
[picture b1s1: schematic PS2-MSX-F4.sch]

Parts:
C1, C5: 100nF; C_Disc_D4.3mm_W1.9mm_P5.00mm
C2, C3: 220pF; C_Disc_D4.3mm_W1.9mm_P5.00mm
C4: 47uF x 10V; CP_Radial_D5.0mm_P2.50mm
F1: 350mA Polyfuse SMD 0603 or 1206; Fuse_1206_0603_3216Metric_Pad1.42x1.75mm_HandSolder
J1: Conn_02x17_Odd_Even; PinHeader_2x17_P2.54mm_Vertical
J2: Conn_01x04; PinSocket_1x04_P2.54mm_Vertical
J3: Conn_01x04; PinHeader_1x04_P2.54mm_Vertical
Q1: 2SC1815; TO-92_Inline
Q2: 2N2907; TO-92_Inline
R1, R2, R3, R4, R5, R6, R7, R8, R9, R17, R18: 22R; R_Axial_DIN0204_L3.6mm_D1.6mm_P7.62mm_Horizontal
R10: 5K6; R_Axial_DIN0204_L3.6mm_D1.6mm_P7.62mm_Horizontal
R11, R12, R13, R16: 10K; R_Axial_DIN0204_L3.6mm_D1.6mm_P7.62mm_Horizontal
R14: 33K; R_Axial_DIN0204_L3.6mm_D1.6mm_P7.62mm_Horizontal
R15: 330K; R_Axial_DIN0204_L3.6mm_D1.6mm_P7.62mm_Horizontal
U1: WeAct Studio STM32F401CEU6 V3.0+ (Black Pill); BlackPill-minif4_board-1

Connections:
+3V3: J2.4, U1.38 (3V3)
+5VD: C1.1, C4.1, C5.1, F1.1, Q2.1 (E), R13.1, R15.1, R16.1, U1.18 (5V)
/3.3V_Serial_RX: J2.3, U1.7 (PA10)
/3.3V_Serial_TX: J2.2, R9.2
/+5V_PS2_Keyboard: J3.1, Q2.3 (C)
/CapsL: R11.1, U1.12 (PB4)
/CapsLed: J1.26, R11.2
/KanaL: R12.1, U1.14 (PB6)
/KanaLed: J1.28, R12.2
/PS2Clk: C2.1, R16.2, R17.1, U1.10 (PA15), U1.15 (PB7)
/PS2ClkPin: J3.2, R17.2
/PS2Data: C3.1, R13.2, R18.1, U1.13 (PB5)
/PS2DataPin: J3.3, R18.2
/X0: J1.2, R1.1
/X0': R1.2, U1.1 (PB12)
/X1: J1.4, R2.1
/X1': R2.2, U1.37 (PB10)
/X2: J1.6, R3.1
/X2': R3.2, U1.2 (PB13)
/X3: J1.8, R4.1
/X3': R4.2, U1.11 (PB3)
/X4: J1.10, R5.1
/X4': R5.2, U1.3 (PB14)
/X5: J1.12, R6.1
/X5': R6.2, U1.35 (PB1)
/X6: J1.14, R7.1
/X6': R7.2, U1.4 (PB15)
/X7: J1.16, R8.1
/X7': R8.2, U1.34 (PB0)
/Y0: J1.18, U1.5 (PA8)
/Y1: J1.20, U1.33 (PA7)
/Y2: J1.22, U1.32 (PA6)
/Y3: J1.24, U1.31 (PA5)
GNDD: C1.2, C2.2, C3.2, C4.2, C5.2, J1.1, J1.3, J1.5, J1.7, J1.9, J1.11, J1.13, J1.15, J1.17, J1.19, J1.21, J1.23, J1.25, J1.27, J1.29, J1.30, J1.31, J1.33, J2.1, J3.4, Q1.1 (E), U1.19 (GND), U1.39 (GND)
unnamed: F1.2, J1.32, J1.34
unnamed: Q1.2 (C), R14.2
unnamed: Q1.3 (B), R10.1
unnamed: Q2.2 (B), R14.1, R15.2
unnamed: R9.1, U1.6 (PA9)
unnamed: R10.2, U1.30 (PA4)

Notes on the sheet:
KANA LED is connected to YM2149 IOB7, pin 6 of DIP package. (Active LOW.) If not used, let pin floating, as it is already connected to an internal pull up.
CAPS LED is connected to PPI 8255 PC6, pin 11 of DIP package. (Active LOW)
October, 31th 2021
PS/2 Adapter for MSX keyboard Project using WeAct Studio STM32F401CCU6 V2.0+ (Black Pill)
Designed by Evandro Souza Free to use as is. For more details, see the technical docs.
Protection only. If you don't want protection, let these resistors short.
Pull up of PS/2 keyboard lines. This is the one that might left open.
Protection only. If you don't want protection, let this resistor short.
This module have the function to cut power of the keyboard connector if it is not detect at power up reset. It's for protection. If you don't need protection, let all components open but short Q2 1-3. put

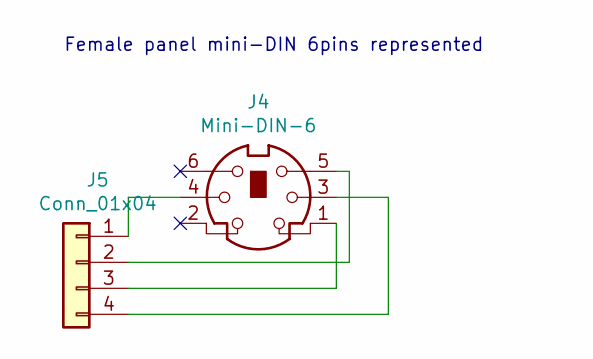
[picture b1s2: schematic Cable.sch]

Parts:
J4: Mini-DIN-6
J5: Conn_01x04

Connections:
unnamed: J4.1, J5.3
unnamed: J4.3, J5.4
unnamed: J4.4, J5.1
unnamed: J4.5, J5.2

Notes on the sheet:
Female panel mini-DIN 6pins represented

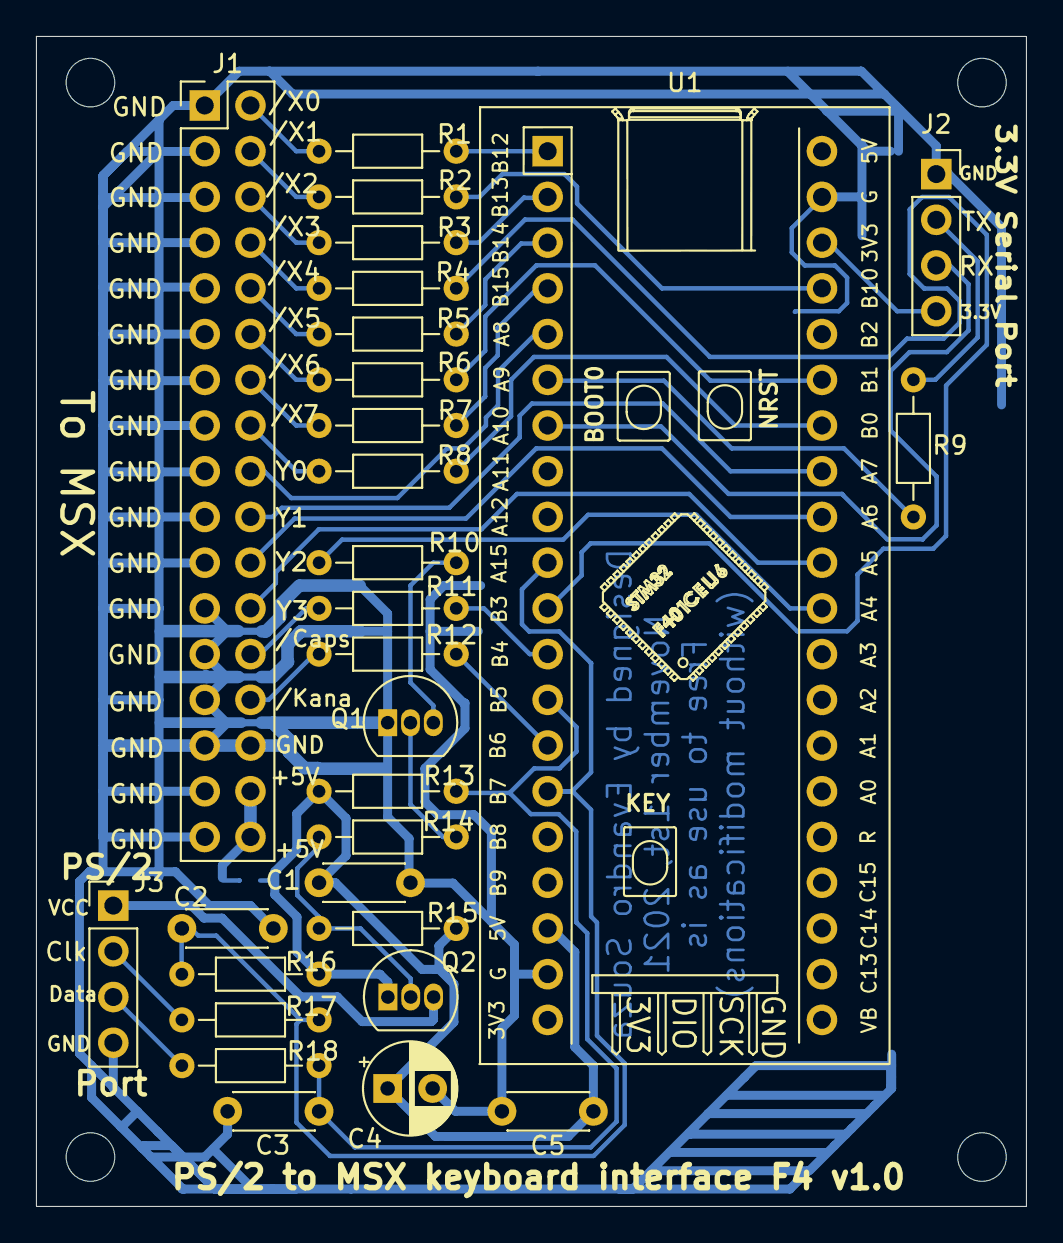
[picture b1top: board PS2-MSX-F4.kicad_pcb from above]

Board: 2 copper layers, 55.0 x 65.0 mm, 30 parts (1 on the bottom side), 40 nets.

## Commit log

2022-05-24 PS/2 to MSX keyboard adapter with USB Console
    USB is "at working" status, to leave the need of a serial adapter to upload the database.
    This is a bare metal design adapter based on STM32F401Mini to attach a PS/2 keyboard to a MSX [or other computers that use a up to 15 (input) x 8 (reading) matrix] with 4 bit BCD input. It has expand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
    This unit has a highly configurable capability, as it has an user updateable database, without need to recompile and upload a new code, to translate from PC keyboard to MSX.
2022-05-24 Update README.md
    STM32F401 with USB console based PS/2 Keyboard adapter for 15x8 matrix(BCD input - 8 bits "Low active" output) , mainly for use in MSX computers.
2022-05-27 README.md update
    STM32F401 with USB console based PS/2 Keyboard adapter for 15x8 matrix(BCD input - 8 bits "Low active" output) , mainly for use in MSX computers.
2022-09-11 PS/2 to MSX keyboard adapter with USB Console
    USB is implemented to be used a console, in aim to leave the need of a serial adapter to upload the database.
    USB is available as DFU (Device Softwqre Update), so you will only need a USB C cable => the same cable used in nowadays mobile phones.
    This is a bare metal design adapter based on Blue Pill or Black Pill F401Mini to attach a PS/2 keyboard to a MSX [or other computers that use a up to 15 (input) x 8 (reading) matrix] with 4 bit BCD i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
    This unit has a highly configurable capability, as it has an user updateable database, without need to recompile and upload a new firmwware, t
2022-09-25 Makefile names target automatically
    This Makefile + rules.mk names target platforms to mitigate confusion on which target we have complied.As my project points two targets: Blue Pill or WeAct MiniF4 Black Pill, that have different layo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
2022-09-25 PS/2 to MSX keyboard adapter with USB Console
    USB is implemented to be used as console, with the target to allow to upload the database through USB.
    USB is available as DFU (Device Softwqre Update), so you will only need a USB C cable => the same cable used in nowadays mobile phones.
    This is a bare metal design adapter based on Blue Pill or Black Pill F401Mini to attach a PS/2 keyboard to a MSX [or other computers that use a up to 15 (input) x 8 (reading) matrix] with 4 bit BCD i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
    This unit has a highly configurable capability, as it has an user updateable database, without need to recompile and upload a new firmwware, to trans
2022-09-26 Database Compiler Excel File
    Database Compiler Excel File update.
    This file has three sheets: HotBit, Expert and Your MSX Definitions. All three are available to compile the Database, in Generated table sheet. You may use HotBit Deinitions as a guide, since it is c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
    After fill data, click on the MSX keyboard picture to run the excel VBA macro, so you have to enable macros in your excel config.
    This file is also able to run in Open Office / LibreOffice family, as compatibilty mode. It will take longer time to run, because it runs on VBA compatibilty mode.
2022-09-26 Presentation file in PDF
    PDF of a Power Point presentation file
2022-09-26 Presentatioin file
    Presentation file in PDF, from a Power Point one.
2022-09-26 Firmware documentation upload
    HTML Doxygen documentation upload
2022-09-28 Presentatioin file
    Presentation file in PDF, from a MS PowerPoint one. Small typing errors corrected.
2022-09-29 Presentation file
    Presentation file in PDF, from a MS PowerPoint one.
2022-10-03 Emglish PDF Presentation file
    English presentation file in PDF, from a MS PowerPoint one.
2022-10-04 English PDF Presentation file
    English presentation file in PDF, from a MS PowerPoint one.
2022-10-04 English PDF Presentation file
    English PDF presentation.
2022-10-04 Schematics and PCB Design
    Here are the Kicad schematics and PCB design, with all Gerber and drill files already extracted., and a zip to send to do a PCB maker to request for prices.
    Obs.: Kicad version is 5.99.
2022-10-05 Kicad schematic and PCB files
    Upload Kicad schematic and PCB files
2022-10-05 Binaries upload
    Binaries generated files
2022-10-05 HTML firmware documentation
    This is a Doxyfile firmware documentation in html format. Start file: index.html.
2022-10-05 Schematic files in pdf format
2022-10-05 Documentation related updates
    Documentation related updates
2022-10-10 Binary files upload
2022-10-10 Bugs correction upload
2022-11-16 R10 valye update
    NPN base resistor update. Valid to PS/2 keyboard supply current up to 50mA.
2022-11-16 NPN base resistor update
2022-11-16 BPB base resistor update
2022-11-17 English PDF Presentation file
    English PDF Presentation
2022-11-24 R10 value update
    An old missing BOM update => R10: NPN base resistor had its value revised. Valid to PS/2 keyboard supply current up to 50mA.
2022-11-25 English Design Presentation
    English Design Presentation with tio-v2.4a update
2022-11-26 English PDF Presentation file
2022-11-28 Database Compiler Excel File
    Database Compiler Excel File update.
    This file has three sheets: HotBit, Expert and Your MSX Definitions. All three are available to compile the Database to Generated table sheet. You may use HotBit Deinitions as a guide, since it is co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
    Some observations on not common keys:
    . Code is mapped to both Alt keys AND ScrollLock;
    . Graph is mapped to both Windows keys;
    . Select is mapped to Menu key;
2022-11-28 English PDF Presentation file
    English PDF Presentation file
2022-12-02 Documentation update
    Documentation update
2022-12-02 Documentation update
2022-12-03 Waning fix since GCC V11.3 Rel1
    Fix warnings of "not implemented and will always fail" on reentrant calls of NEWLIB from August 8th, 2022, on version 11.3 Rel1.
2022-12-03 Binary files upload
    Binary files upload
2022-12-05 Kicad schematic and PCB files
    Kicad schematic and PCB files upload
2022-12-10 File fixes
    Correction of line 586
2022-12-10 English PDF Presentation file
    English PDF Presentation file with correct name.
2022-12-22 Last minute clean up
    Documentation update including ARM GNU updated toolchain and last minute code cleanups.
2023-02-02 USB Equipment Description update
    Arrange USB Equipment Description to match system.h
2023-02-06 Correct README.md
    Upload the correct README.md
2023-02-06 Upload the correct files
    Upload the correct files
2023-04-30 Technical Presentation File (English)
    Last update was with a wrong file.
2023-04-30 Updated to (Build arm-12-mpacbti.34)
    Generated files to be uploaded, README.md and source code compiled with an Arm GNU Toolchain 12.2.1 20230214 (Arm GNU Toolchain 12.2.MPACBTI-Rel1 (Build arm-12-mpacbti.34)).
2023-11-04 Add F11 mapped to \ and ^ on HB-8000
    Add F11 mapped to "\^" on HB-8000, to get direct access to ASCII "^" (0x5E) on HB-8000 brazilian MSX, as ABNT-2 PS/2 have only one key, used as vogals accent. If you want a ASCII "^" (0x5E) in PC, yo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
    F12 was already mapped to MSX STOP key, as F6 to F10 to MSX Shift plus F1 to F5.
    PS/2 ScrollLock key is mapped to MSX CODE, as also Alt and AltGr keys are.
2023-11-04 Updated to (Arm GNU Toolchain 12.3.1 20230626)
    Generated files to be uploaded, README.md and source code compiled with an Arm GNU Toolchain 12.3.1 20230626 (Arm GNU Toolchain 12.3.Rel1 (Build arm-12.35)).
2023-11-04 Doxygen documentation related correction
    No logic corrections. Only Doxygen documentation related correction updates.
2023-11-04 PS/2 to MSX Database compiler - Add mapped F11
    Important: "Your MSX" sheet mapping is NOT destinated do japanese MSX, but for international ones!
    PS/2 ScrollLock key is mapped to MSX CODE, as also Alt and AltGr keys are. This a fixed functionality in the software;
    Now, follow the "HB-8000" updates:
    Add F11 mapped to "\^" on HB-8000, to get direct access to ASCII "^" (0x5E) on HB-8000 brazilian MSX, as ABNT-2 PS/2 have only one key, used as vogals accent. If you want a ASCII "^" (0x5E) in PC, yo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
    F12 was already mapped to MSX STOP key, as F6 to F10 to MSX Shift plus F1 to F5.
2023-11-04 Introduction page updated
2023-11-04 Compressed html files of Firmware documentation
    No logic corrections. Only Doxygen documentation related correction updates.
2023-11-13 Update README.md
    Fixed details and some typing corrections.
2023-11-13 Update README.md
    Fixed some details and typing errors.
2023-11-13 Update README.md
    Fixed details and some typing errors.
2023-11-13 Update README.md
    Details fixed and typing errors.
2023-11-14 Updated README.md
    Details fixed and typing errors.
2023-11-14 Add files via upload
    Details fixed and typing errors.
2023-11-15 Add files via upload
    Details and typing errors fixed.
2023-11-16 Updated README.md
    README.md small fixes and its update to Doxygen documentation.
2023-11-25 Documentation update due to README.md
    Documentation update due to README.md - Minor upgrade
2023-11-25 Documentation update due to README.md update
    Documentation update due to README.md update - Minor upgrade
2024-04-26 Updated to (Arm GNU Toolchain 13.2.Rel1 20231030)
    Generated files to be uploaded, README.md and source code compiled with an Arm GNU Toolchain 13.2.Rel1 20231030.
2024-04-27 Update Makefile
2024-09-21 Upload to support Arm GNU Toolchain 13.3.Rel1
    Uploaded files made with Arm GNU Toolchain 13.3.Rel1 Released: July 4, 2024
2024-09-21 Made with Arm GNU Toolchain 13.3.Rel1
    Uploaded files made with Arm GNU Toolchain 13.3.Rel1 Released: July 4, 2024
2025-04-20 Arm GNU Toolchain 14.2.Rel1 Updated
    Updated due to Arm GNU Toolchain 14.2.Rel1 Released: December 10, 2024
2025-04-20 Files updated due to Arm GNU Toolchain 14.2.Rel1
    Files updated due to Arm GNU Toolchain 14.2.Rel1 Released: December 10, 2024
